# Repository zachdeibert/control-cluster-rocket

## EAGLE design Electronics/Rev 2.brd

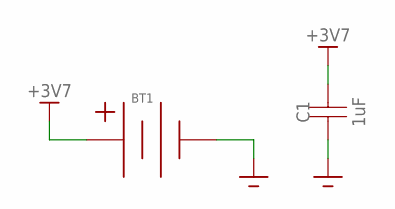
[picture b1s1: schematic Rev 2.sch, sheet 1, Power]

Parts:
BT1: 18650
C1: 1uF; 0805

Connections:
+3V7: BT1.+1 (+), BT1.+2 (+), BT1.+3 (+), C1.P$2; also elsewhere on the board
GND: BT1.-1 (-), BT1.-2 (-), BT1.-3 (-), C1.P$1; also elsewhere on the board

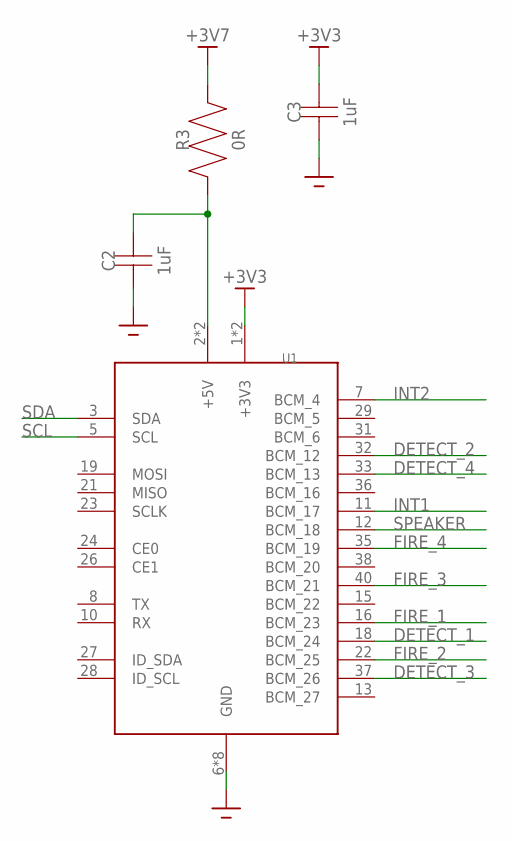
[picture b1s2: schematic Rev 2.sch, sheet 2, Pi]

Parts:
C2, C3: 1uF; 0805
R3: 0R; 0805
U1: RPI-ZERO

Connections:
+3V3: C3.P$2, U1.1 (+3V3), U1.17 (+3V3); also elsewhere on the board
+3V7: R3.P$2; also elsewhere on the board
DETECT_1: U1.18 (BCM_24); also elsewhere on the board
DETECT_2: U1.32 (BCM_12); also elsewhere on the board
DETECT_3: U1.37 (BCM_26); also elsewhere on the board
DETECT_4: U1.33 (BCM_13); also elsewhere on the board
FIRE_1: U1.16 (BCM_23); also elsewhere on the board
FIRE_2: U1.22 (BCM_25); also elsewhere on the board
FIRE_3: U1.40 (BCM_21); also elsewhere on the board
FIRE_4: U1.35 (BCM_19); also elsewhere on the board
GND: C2.P$1, C3.P$1, U1.6 (GND), U1.9 (GND), U1.14 (GND), U1.20 (GND), U1.25 (GND), U1.30 (GND), U1.34 (GND), U1.39 (GND); also elsewhere on the board
INT1: U1.11 (BCM_17); also elsewhere on the board
INT2: U1.7 (BCM_4); also elsewhere on the board
unnamed: C2.P$2, R3.P$1, U1.2 (+5V), U1.4 (+5V)
SCL: U1.5 (SCL); also elsewhere on the board
SDA: U1.3 (SDA); also elsewhere on the board
SPEAKER: U1.12 (BCM_18); also elsewhere on the board

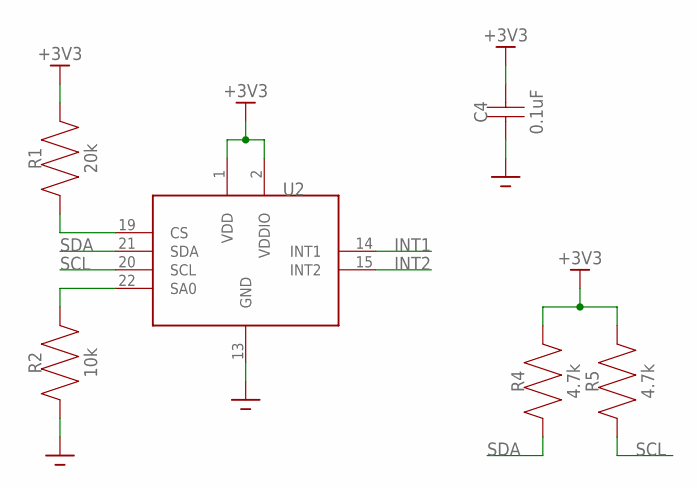
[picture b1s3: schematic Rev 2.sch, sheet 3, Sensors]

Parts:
C4: 0.1uF; 0805
R1: 20k; 0805
R2: 10k; 0805
R4, R5: 4.7k; 0805
U2: STEVAL-MKIT01V1; DIP1524W53P254L3302H1000Q24B

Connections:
+3V3: C4.P$2, R1.P$2, R4.P$2, R5.P$2, U2.1 (VDD), U2.2 (VDDIO); also elsewhere on the board
GND: C4.P$1, R2.P$1, U2.13 (GND); also elsewhere on the board
INT1: U2.14 (INT1); also elsewhere on the board
INT2: U2.15 (INT2); also elsewhere on the board
unnamed: R1.P$1, U2.19 (CS)
unnamed: R2.P$2, U2.22 (SA0)
SCL: R5.P$1, U2.20 (SCL); also elsewhere on the board
SDA: R4.P$1, U2.21 (SDA); also elsewhere on the board

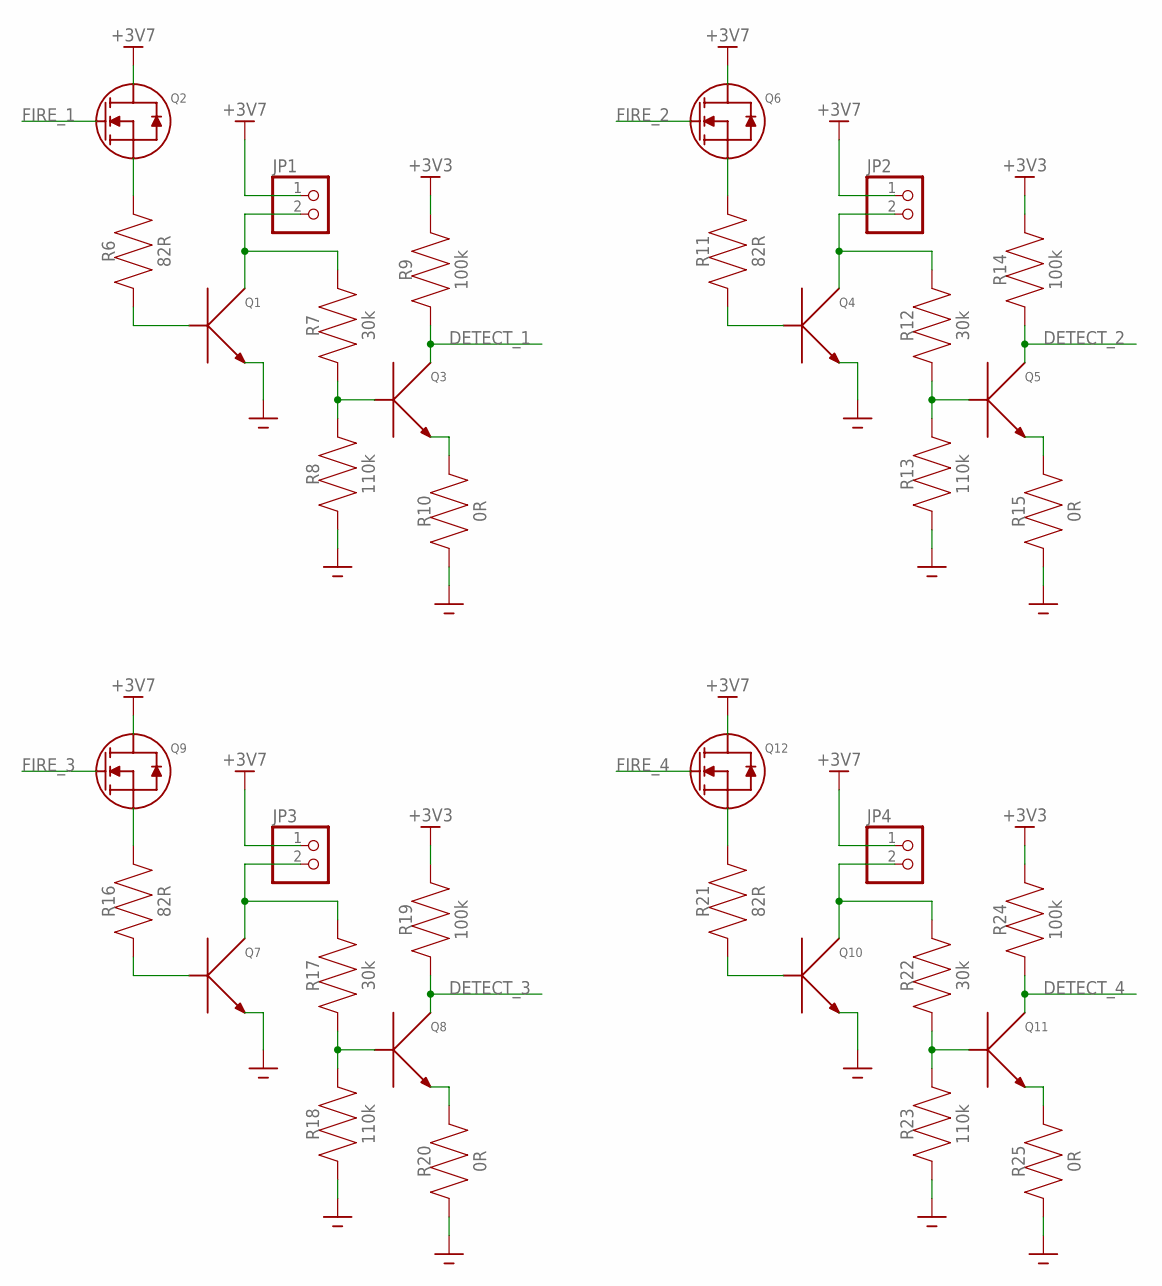
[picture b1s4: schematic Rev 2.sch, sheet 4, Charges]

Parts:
JP1, JP2, JP3, JP4: PINHD-1X2; 1X02
Q1, Q4, Q7, Q10: 3STF1640
Q2, Q6, Q9, Q12: DMN601K; SOT91P240X110-3
Q3, Q5, Q8, Q11: MMBT3904; SOT96P237X112-3
R6, R11, R16, R21: 82R; 0805
R7, R12, R17, R22: 30k; 0805
R8, R13, R18, R23: 110k; 0805
R9, R14, R19, R24: 100k; 0805
R10, R15, R20, R25: 0R; 0805

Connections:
+3V3: R9.P$2, R14.P$2, R19.P$2, R24.P$2; also elsewhere on the board
+3V7: JP1.1, JP2.1, JP3.1, JP4.1, Q2.3 (D), Q6.3 (D), Q9.3 (D), Q12.3 (D); also elsewhere on the board
DETECT_1: Q3.3 (C), R9.P$1; also elsewhere on the board
DETECT_2: Q5.3 (C), R14.P$1; also elsewhere on the board
DETECT_3: Q8.3 (C), R19.P$1; also elsewhere on the board
DETECT_4: Q11.3 (C), R24.P$1; also elsewhere on the board
FIRE_1: Q2.1 (G); also elsewhere on the board
FIRE_2: Q6.1 (G); also elsewhere on the board
FIRE_3: Q9.1 (G); also elsewhere on the board
FIRE_4: Q12.1 (G); also elsewhere on the board
GND: Q1.P3 (E), Q4.P3 (E), Q7.P3 (E), Q10.P3 (E), R8.P$1, R10.P$1, R13.P$1, R15.P$1, R18.P$1, R20.P$1, R23.P$1, R25.P$1; also elsewhere on the board
unnamed: Q2.2 (S), R6.P$2
unnamed: JP1.2, Q1.P2 (C), Q1.P4 (C), Q1.P5 (C), R7.P$2
unnamed: Q3.2 (E), R10.P$2
unnamed: Q1.P1 (B), R6.P$1
unnamed: Q3.1 (B), R7.P$1, R8.P$2
unnamed: Q6.2 (S), R11.P$2
unnamed: JP2.2, Q4.P2 (C), Q4.P4 (C), Q4.P5 (C), R12.P$2
unnamed: Q4.P1 (B), R11.P$1
unnamed: Q5.1 (B), R12.P$1, R13.P$2
unnamed: Q5.2 (E), R15.P$2
unnamed: Q9.2 (S), R16.P$2
unnamed: JP3.2, Q7.P2 (C), Q7.P4 (C), Q7.P5 (C), R17.P$2
unnamed: Q7.P1 (B), R16.P$1
unnamed: Q8.1 (B), R17.P$1, R18.P$2
unnamed: Q8.2 (E), R20.P$2
unnamed: Q12.2 (S), R21.P$2
unnamed: JP4.2, Q10.P2 (C), Q10.P4 (C), Q10.P5 (C), R22.P$2
unnamed: Q10.P1 (B), R21.P$1
unnamed: Q11.1 (B), R22.P$1, R23.P$2
unnamed: Q11.2 (E), R25.P$2

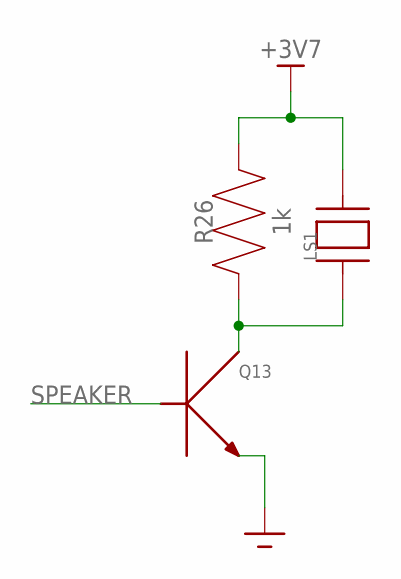
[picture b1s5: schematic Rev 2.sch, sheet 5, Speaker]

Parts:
LS1: PKM13EPYH4000-A0
Q13: MMBT3904; SOT96P237X112-3
R26: 1k; 0805

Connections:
+3V7: LS1.P2, R26.P$2; also elsewhere on the board
GND: Q13.2 (E); also elsewhere on the board
unnamed: LS1.P1, Q13.3 (C), R26.P$1
SPEAKER: Q13.1 (B); also elsewhere on the board

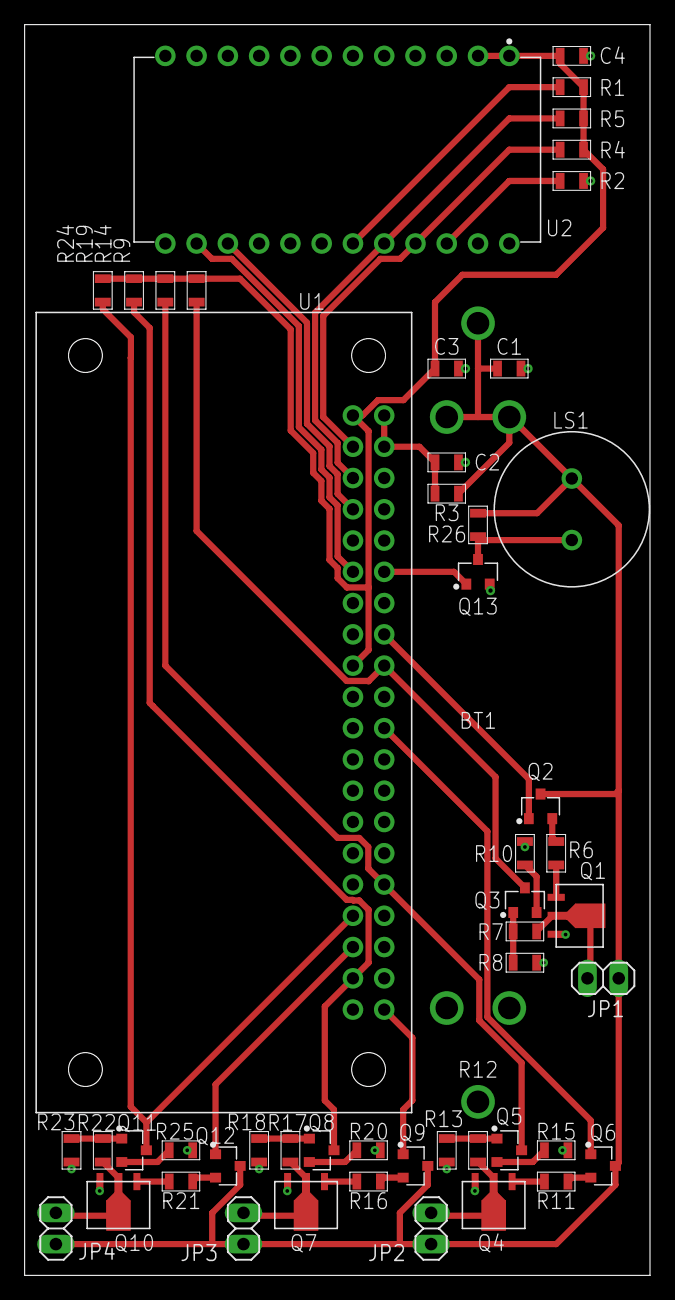
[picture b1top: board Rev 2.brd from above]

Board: 2 copper layers, 50.8 x 101.6 mm, 51 parts (1 on the bottom side), 40 nets.

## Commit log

2019-04-07 Created project file
2019-04-07 Created the sensor breakouts
2019-04-07 Added other schematic parts
2019-04-07 Added schematic for sensors
2019-04-07 Created firing circuits
2019-04-07 Stole the buck converter from Madeline's project
2019-04-07 Added buck converter circuit
2019-04-07 Fixed ERC
2019-04-07 Routed initial version of board
2019-04-10 Connected the two grounds
2019-04-10 Added planes
2019-04-10 Added rocket model
2019-04-10 Moved silk screen around
2019-04-10 Created gerbers
2019-04-16 Updated PCB manufacturing files
2019-04-16 Modeled rocket
2019-04-18 Created engine file parser
2019-04-18 Updated RockSim file to include boosters
2019-04-18 Created rocket model parser
2019-04-18 Added physics simulator
2019-04-29 Added some optimization methods
2019-05-01 Added flight optimization code
2019-05-01 Added MQTT code
2019-05-01 Started test code
2019-05-02 Wrote code to send flight profile over the bus
2019-07-26 Removed old board files
2019-07-27 Created schematic
2019-07-27 Layed out the rev 2 board
2019-07-27 Organized reference designators
2019-07-27 Added more to the silk screen
2019-07-27 Made DRC happy
2019-09-09 Finished electronics
2019-09-09 Updated gitignore
2019-09-09 Created antenna parts
2019-09-09 Added lip to upper electronics coupler
2019-09-13 Removed old STL files
